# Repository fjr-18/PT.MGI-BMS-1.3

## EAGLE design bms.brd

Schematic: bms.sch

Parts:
C1, C12: 1uF; C0805K
C2, C3: 22pF; C0805K
C5, C7, C9, C11, C19: 10uF; C0805K
C6, C8, C10, C14: 100nF; C0805K
C25: 10uF/16v; 153CLV-0505
C26: 10uF/16V; 153CLV-0505
CONN2P-3.5PI1, CONN2P-3.5PI2, CONN2P-3.5PI3: CONN2P-3.5PI
CONN3.1: CONN3.5
D1, D6: SML-LXT0805IW-TR; LEDC2012X120N
D5, D9: 1N5819HW-7; SOD3715X145N
HEADER-3.81-1: HEADER-3.81-4
IC1: MCP23017SS; SSOP28
J1: U.FL-R-SMT(01); HRS_U.FL-R-SMT(01)
J3: 10103594
JP1, JP2, JP3, JP4: PINHD-1X3; 1X03
LORA-NICERF-V1: LORA-NICERF-V2
MD1: ESPRESSIF_SYSTEMS_ESP32-WROOM-32U_16MBESPRESSIF_S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; ESPRESSIF_SYSTEMS_ESP32-WROOM-32U_16MB_0
POWER: TLLY4400; LED3MM
PROSES: TLLY4400; LED3MM
PS1: URB2405YMD-10WR3; URB2405YMD10WR3
Q1, Q2: MMBT3904; SOT95P240X120-3N
Q3: 12MHz; SM49
R1, R2, R7, R8: 10K; M0805
R3, R4, R5, R12, R13: 1K; M0805
R6, R9, R10, R11, R14, R15: 10k; M0805
R16: 4.7K; M0805
R17, R18, R19, R20: 100; M0805
S3, S4: TL1015AF160QG; SW_TL1015AF160QG
TTL-RS1, TTL-RS2: TTL-RS485
U1, U2: RT9193-33GB; SOT94P279X129-5N
U$2: CH340G; SOIC16
WARNING: TLLY4400; LED3MM

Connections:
1WIRE: CONN3.1.P5, CONN3.1.P6, CONN3.1.P7, CONN3.1.P8, MD1.26 (IO4), R16.2
3V3: C9.1, MD1.2 (3V3), R4.2, R5.2, R7.1, R8.1, U1.5 (VOUT)
3V3-LORA-RS232: C7.2, C8.2, C19.1, LORA-NICERF-V1.VCC, U2.5 (VOUT)
ANT: J1.3 (SIG), LORA-NICERF-V1.ANT
DTR: Q2.2 (E), R1.1, U$2.13 (DTR)
EN: C14.2, MD1.3 (EN), Q1.3 (C), R7.2, S3.1
GND: C1.2, C2.2, C3.2, C5.2, C6.2, C7.1, C8.1, C9.2, C10.1, C11.2, C12.2, C14.1, C19.2, C25.-, C26.-, CONN2P-3.5PI1.P1, HEADER-3.81-1.P$1 (1), HEADER-3.81-1.P$2 (2), IC1.10 (VSS), J1.1 (GND), J1.2 (GND), J3.5 (GND), J3.6 (SHIELD5), J3.7 (SHIELD6), J3.SH1 (SHIELD1), J3.SH2 (SHIELD2), J3.SH3 (SHIELD3), J3.SH4 (SHIELD4), LORA-NICERF-V1.GND, LORA-NICERF-V1.GND1, MD1.1 (1_GND), MD1.15 (2_GND), MD1.38 (3_GND), MD1.39 (4_GND), MD1.39-2 (4_GND), MD1.39-3 (4_GND), MD1.39-4 (4_GND), MD1.39-5 (4_GND), MD1.39-6 (4_GND), MD1.39-7 (4_GND), MD1.39-8 (4_GND), MD1.39-9 (4_GND), POWER.K (C), PROSES.K (C), PS1.1 (GND), PS1.5 (0V), R11.2, R14.2, R15.2, S3.2, S4.2, TTL-RS1.GND, TTL-RS2.GND, U1.2 (GND), U2.2 (GND), U$2.1 (GND), WARNING.K (C)
GPA0: IC1.21 (GPA0), JP1.1
GPA1: IC1.22 (GPA1), JP2.1
GPA2: IC1.23 (GPA2), JP3.1
GPA3: IC1.24 (GPA3), JP4.1
GPB0: IC1.1 (GPB0), JP1.3
GPB1: IC1.2 (GPB1), JP2.3
GPB2: IC1.3 (GPB2), JP3.3
GPB3: IC1.4 (GPB3), JP4.3
IO0: C10.2, MD1.25 (IO0), Q2.3 (C), R8.2, S4.1
LED_PROSES: MD1.12 (IO27), R12.2
LED_WARNING: MD1.9 (IO33), R13.2
LORA_DI0: LORA-NICERF-V1.DIO0, MD1.8 (IO32)
LORA_DI1: LORA-NICERF-V1.DIO1, MD1.10 (IO25)
MISO_VSPI: LORA-NICERF-V1.MISO, MD1.31 (IO19)
MOSI_VSPI: LORA-NICERF-V1.MOSI, MD1.37 (IO23)
unnamed: C2.1, Q3.1, U$2.7 (XI)
unnamed: C3.1, Q3.2, U$2.8 (XO)
unnamed: POWER.A, R3.1
unnamed: Q1.1 (B), R1.2
unnamed: Q2.1 (B), R2.2
unnamed: CONN2P-3.5PI3.P1, TTL-RS2.A
unnamed: CONN2P-3.5PI2.P1, TTL-RS1.A
unnamed: D1.A, R4.1
unnamed: D6.A, R5.1
unnamed: CONN2P-3.5PI2.P0, TTL-RS1.B
unnamed: CONN2P-3.5PI1.P0, PS1.2 (VIN), PS1.6 (CTRL)
unnamed: C6.1, U$2.4 (V3)
unnamed: CONN2P-3.5PI3.P0, TTL-RS2.B
unnamed: IC1.18 (!RESET), R6.1
unnamed: CONN3.1.P4, R20.1
unnamed: D9.A, PS1.3 (+VO)
unnamed: CONN3.1.P3, R19.1
unnamed: IC1.15 (A0), R11.1
unnamed: IC1.16 (A1), R14.1
unnamed: IC1.17 (A2), R15.1
unnamed: CONN3.1.P2, R18.1
unnamed: CONN3.1.P1, R17.1
unnamed: PROSES.A, R12.1
unnamed: R13.1, WARNING.A
OUT+: C5.1, C11.1, C12.1, C26.+, D5.C (K), D9.C (K), HEADER-3.81-1.P$3 (3), HEADER-3.81-1.P$4 (4), IC1.9 (VDD), R3.2, R6.2, R9.2, R10.2, R16.1, TTL-RS1.VCC, TTL-RS2.VCC, U1.1 (VIN), U1.3 (EN), U2.1 (VIN), U2.3 (EN)
PO1: JP1.2, R17.2
PO2: JP2.2, R18.2
PO3: JP3.2, R19.2
PO4: JP4.2, R20.2
RST_LORA: LORA-NICERF-V1.NRST, MD1.11 (IO26)
RTS: Q1.2 (E), R2.1, U$2.14 (RTS)
RX: D6.C, MD1.35 (TXD0), U$2.3 (RX)
RX-PZEM: MD1.23 (IO15), TTL-RS2.RX
RX-RS485: MD1.28 (IO17), TTL-RS1.RX
SCK_VSPI: LORA-NICERF-V1.SCK, MD1.30 (IO18)
SCL: IC1.12 (SCL), MD1.36 (IO22), R9.1
SDA: IC1.13 (SDA), MD1.33 (IO21), R10.1
SS_LORA: LORA-NICERF-V1.NSS, MD1.29 (IO5)
TX: D1.C, MD1.34 (RXD0), U$2.2 (TX)
TX-PZEM: MD1.13 (IO14), TTL-RS2.TX
TX-RS485: MD1.27 (IO16), TTL-RS1.TX
USB_N: J3.2 (D-), U$2.6 (D-)
USB_P: J3.3 (D+), U$2.5 (D+)
VCC: C1.1, C25.+, D5.A, J3.1 (VCC), U$2.16 (VCC)

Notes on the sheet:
CH340 DRIVER
POWER
ESP32U-WROOM
AUTO RESET
LoRa niceRF

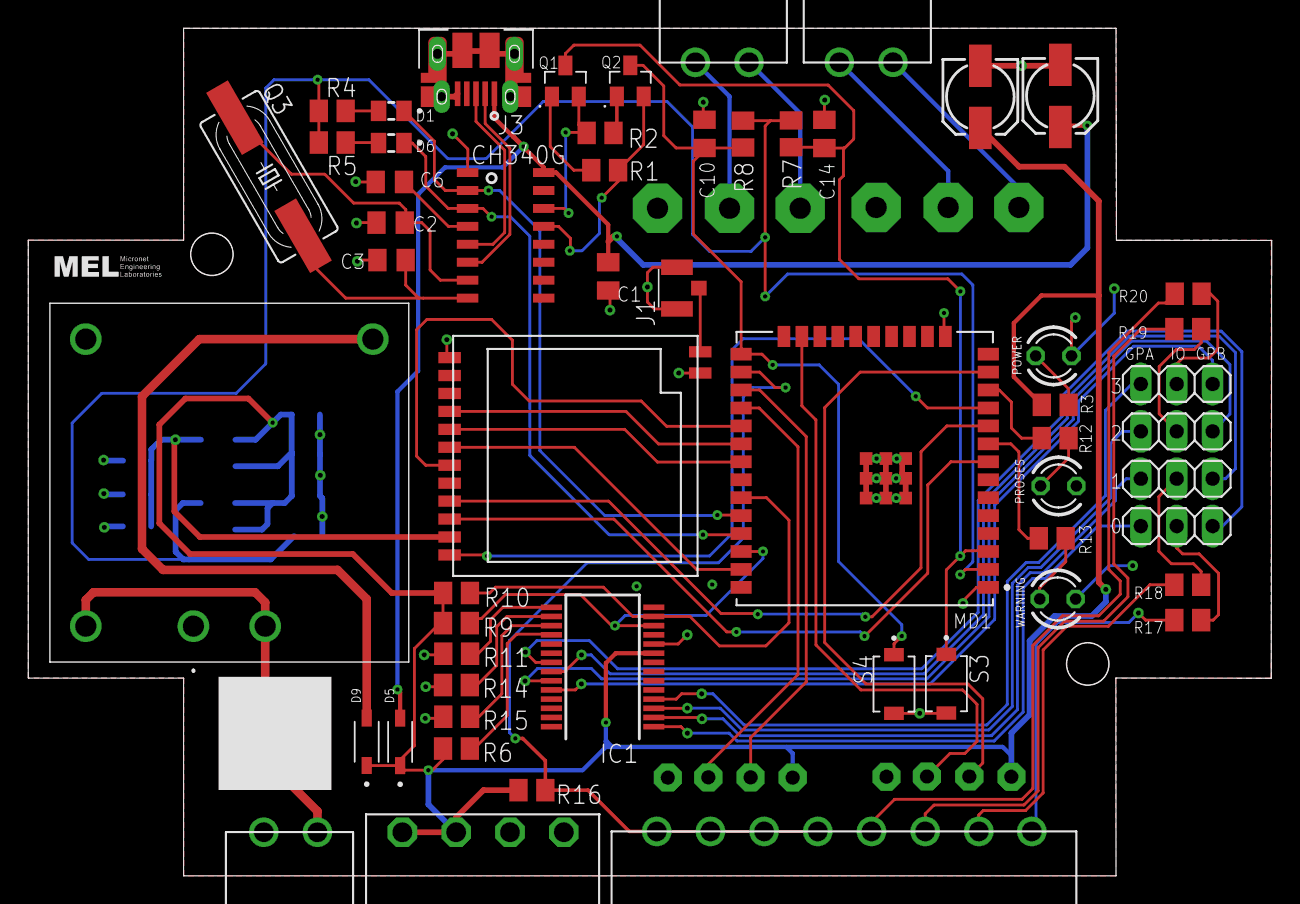
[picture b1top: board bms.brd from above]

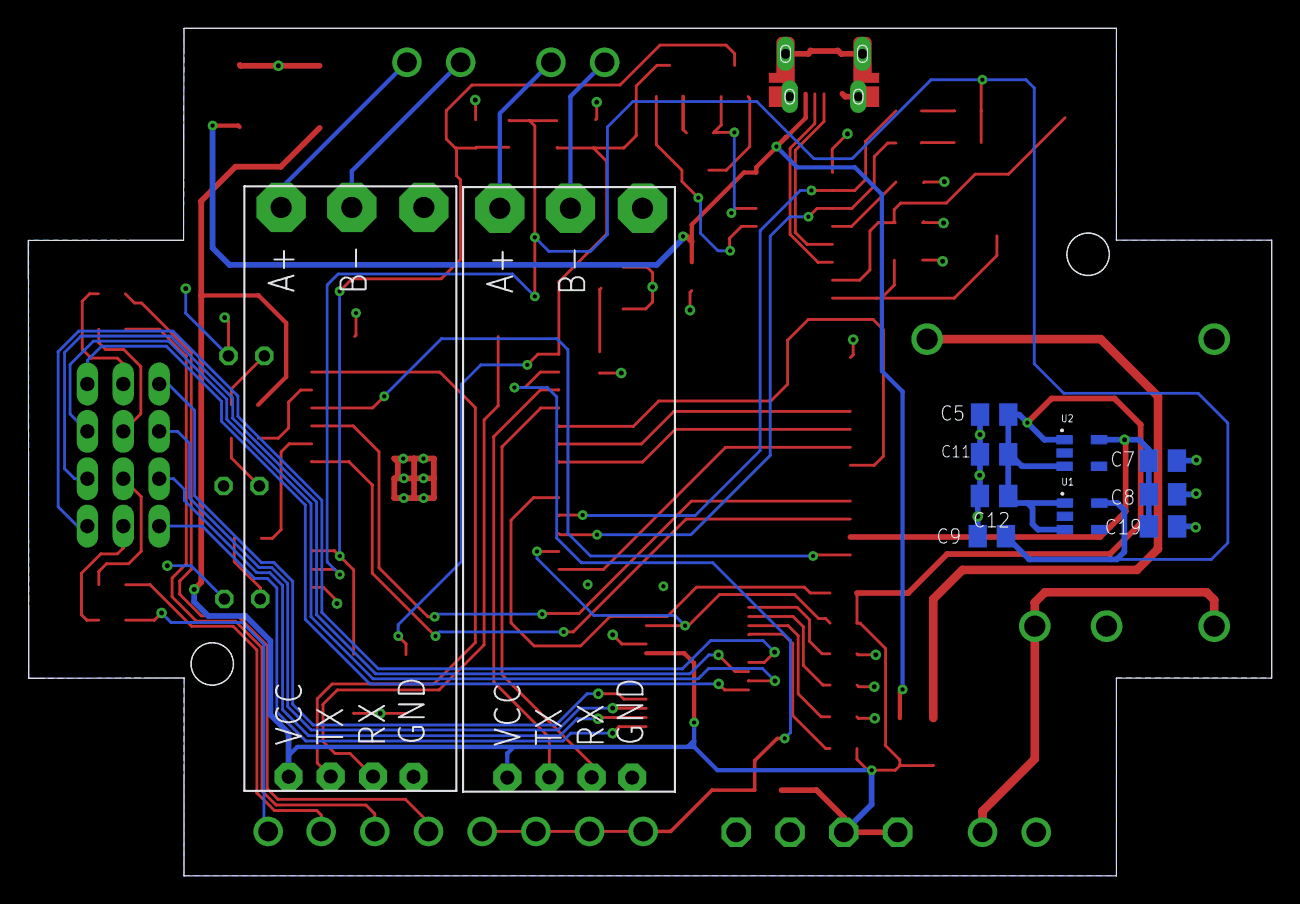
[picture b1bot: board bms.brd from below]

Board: 2 copper layers, 88.0 x 60.0 mm, 67 parts (11 on the bottom side), 66 nets.

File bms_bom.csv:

Comment,Designator,Footprint,LCSC Part #
,JP1,1X03,
,JP2,1X03,
,JP3,1X03,
,JP4,1X03,
,CONN2P-3.5PI1,CONN2P-3.5PI,
,CONN2P-3.5PI2,CONN2P-3.5PI,
,CONN2P-3.5PI3,CONN2P-3.5PI,
,CONN3.1,CONN3.5,
,HEADER-3.81-1,HEADER-3.81-4,
,LORA-NICERF-V1,LORA-NICERF-V2,
,TTL-RS1,TTL-RS485,
,TTL-RS2,TTL-RS485,
1K,R3 R4 R5 R12 R13,M0805,
1N5819HW-7,D5 D9,SOD3715X145N,
1uF,C1 C12,C0805K,
4.7K,R16,M0805,
10K,R1 R2 R7 R8,M0805,
10k,R6 R9 R10 R11 R14 R15,M0805,
10uF,C5 C7 C9 C11 C19,C0805K,
10uF/16V,C26,153CLV-0505,
10uF/16v,C25,153CLV-0505,
12MHz,Q3,SM49,
22pF,C2 C3,C0805K,
100,R17 R18 R19 R20,M0805,
100nF,C6 C8 C10 C14,C0805K,
10103594,J3,10103594,
CH340G,U$2,SOIC16,
ESPRESSIF_SYSTEMS_ESP32-WROOM-32U_16MBESPRESSIF_SYSTEMS_ESP32-WROOM-32U_16MB_0_0,MD1,ESPRESSIF_SYSTEMS_ESP32-WROOM-32U_16MB_0,
MCP23017SS,IC1,SSOP28,
MMBT3904,Q1 Q2,SOT95P240X120-3N,
RT9193-33GB,U1 U2,SOT94P279X129-5N,
SML-LXT0805IW-TR,D1 D6,LEDC2012X120N,
TL1015AF160QG,S3 S4,SW_TL1015AF160QG,
TLLY4400,POWER PROSES WARNING,LED3MM,
U.FL-R-SMT(01),J1,HRS_U.FL-R-SMT(01),
URB2405YMD-10WR3,PS1,URB2405YMD10WR3,
